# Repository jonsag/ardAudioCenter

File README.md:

# ardAudioCenter

An arduino used as a center for audio control.  
Selects between inputs, sets volume, balance etc.  
Controls an FM radio receiver.  
Has an LCD screen.  

## Note

This is a work in progress, but should now be working.  

## Parts list (incomplete)

1 x Arduino (I use and Arduino Nano, ElectroKit#41015511)  
1 x TEA5767 FM radio module, ElectroKit#41015747  
1 x DFPlayer Mini  
1 x CD4052B multiplexer, ElectroKit#40360102  
2 x MCP41010-E/P digital potentiometer, ElectroKit#40351010  
1 x LCD screen, 2x16, ElectroKit#41001407  
1 x Serial interface for LCD, ElectroKit#41011443  
2 x Rotary encoder, ElectroKit#41015725

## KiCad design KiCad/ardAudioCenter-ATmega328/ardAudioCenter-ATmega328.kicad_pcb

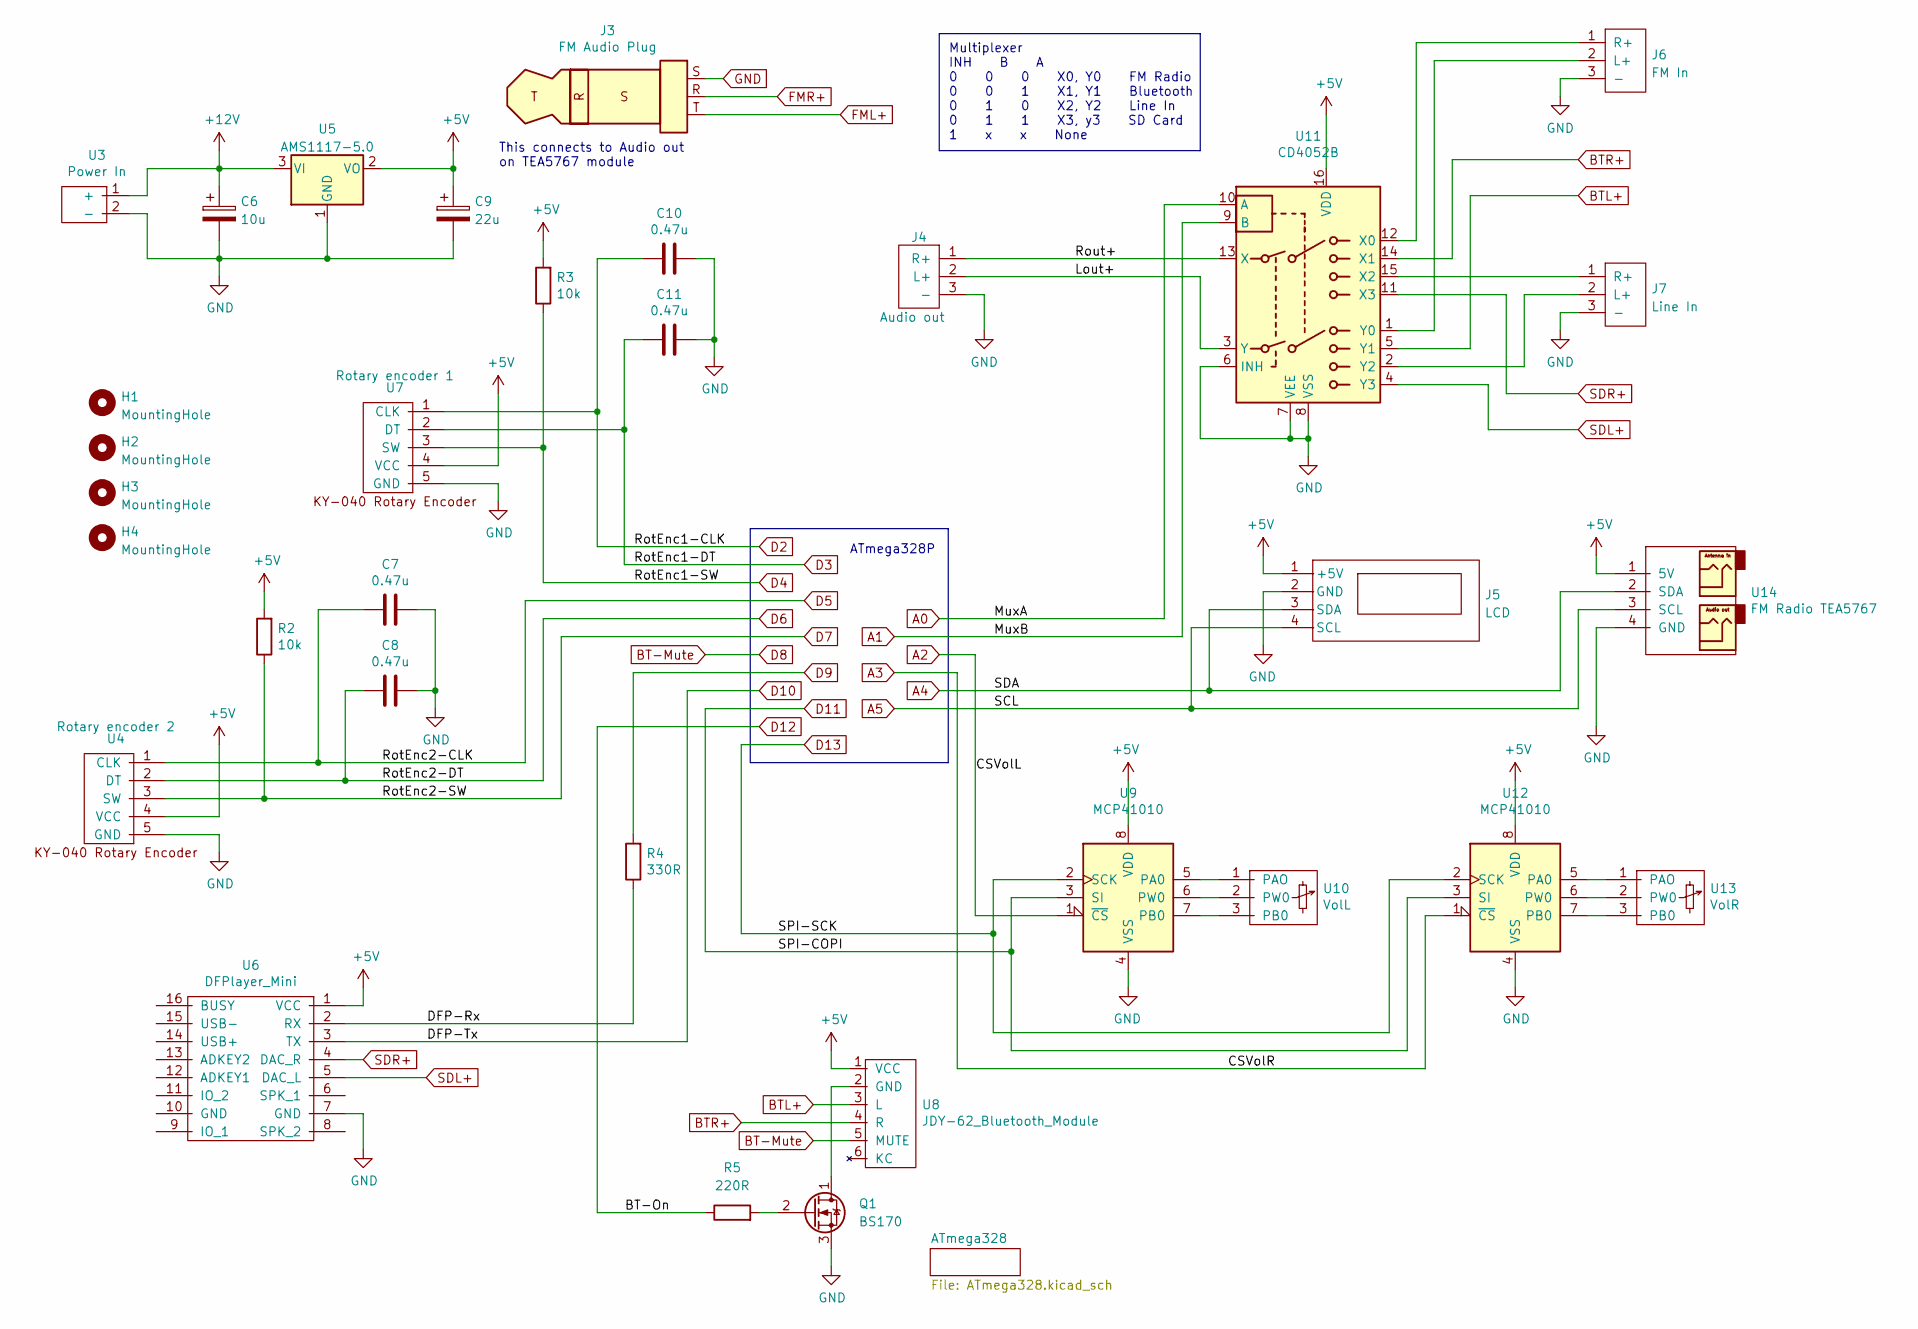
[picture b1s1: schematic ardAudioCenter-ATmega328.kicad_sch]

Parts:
C6: 10u; CP_Radial_D5.0mm_P2.00mm_larger
C7, C8, C10, C11: 0.47u; C_Disc_D7.5mm_W2.5mm_P5.00mm_larger
C9: 22u; CP_Radial_D5.0mm_P2.00mm_larger
H1, H2, H3, H4: MountingHole; MountingHole_3.5mm
J3: FM Audio Plug
J4: Audio out; 3-pin JST Audio
J5: LCD; 4-pin JST LCD
J6: FM In; 3-pin JST Audio
J7: Line In; 3-pin JST Audio
Q1: BS170; TO-92_Inline_Wide_large
R2, R3: 10k; R_Axial_DIN0207_L6.3mm_D2.5mm_P10.16mm_Horizontal_larger_pa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
R4: 330R; R_Axial_DIN0207_L6.3mm_D2.5mm_P10.16mm_Horizontal_larger_pa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
R5: 220R; R_Axial_DIN0207_L6.3mm_D2.5mm_P10.16mm_Horizontal_larger_pa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
U3: Power In; 2-pole_power_in_screw_terminal
U4: Rotary encoder 2; 5-pin JST Rotary Encoder
U5: AMS1117-5.0; SOT-223-3_TabPin2
U6: DFPlayer_Mini; 8-pin JST DFPlayer Mini
U7: Rotary encoder 1; 5-pin JST Rotary Encoder
U8: JDY-62_Bluetooth_Module; 6-pin JST JDY-62 Bluetooth
U9, U12: MCP41010; DIP-8_W7.62mm_Socket_w_dip_packet_LongPads
U10: VolL; 3-pin JST Potentiometer
U11: CD4052B; DIP-16_W7.62mm_LongPads w socket
U13: VolR; 3-pin JST Potentiometer
U14: FM Radio TEA5767; 4-pin JST TEA5767 FM Radio

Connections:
+5V: C9.1, J5.1 (+5V), R2.2, R3.2, U4.4 (VCC), U5.2 (VO), U6.1 (VCC), U7.4 (VCC), U8.1 (VCC), U9.8 (VDD), U11.16 (VDD), U12.8 (VDD), U14.1 (5V); also elsewhere on the board
+12V: C6.1, U3.1 (+), U5.3 (VI)
/DFP-Rx: R4.1, U6.2 (RX)
/Lout+: J4.2 (L+), U11.3 (Y)
/Rout+: J4.1 (R+), U11.13 (X)
A0: U11.10 (A); also elsewhere on the board
A1: U11.9 (B); also elsewhere on the board
A2: U9.1 (~CS); also elsewhere on the board
A3: U12.1 (~CS); also elsewhere on the board
A4: J5.3 (SDA), U14.2 (SDA); also elsewhere on the board
A5: J5.4 (SCL), U14.3 (SCL); also elsewhere on the board
BT-Mute: U8.5 (MUTE); also elsewhere on the board
BTL+: U8.3 (L), U11.5 (Y1)
BTR+: U8.4 (R), U11.14 (X1)
D2: C10.1, U7.1 (CLK); also elsewhere on the board
D3: C11.2, U7.2 (DT); also elsewhere on the board
D4: R3.1, U7.3 (SW); also elsewhere on the board
D5: C7.1, U4.1 (CLK); also elsewhere on the board
D6: C8.2, U4.2 (DT); also elsewhere on the board
D7: R2.1, U4.3 (SW); also elsewhere on the board
D9: R4.2; also elsewhere on the board
D10: U6.3 (TX); also elsewhere on the board
D11: U9.3 (SI), U12.3 (SI); also elsewhere on the board
D12: R5.1; also elsewhere on the board
D13: U9.2 (SCK), U12.2 (SCK); also elsewhere on the board
GND: C6.2, C7.2, C8.1, C9.2, C10.2, C11.1, J4.3 (-), J5.2 (GND), J6.3 (-), J7.3 (-), Q1.3 (S), U3.2 (-), U4.5 (GND), U5.1 (GND), U6.7 (GND), U7.5 (GND), U9.4 (VSS), U11.6 (INH), U11.7 (VEE), U11.8 (VSS), U12.4 (VSS), U14.4 (GND); also elsewhere on the board
unnamed: J6.1 (R+), U11.12 (X0)
unnamed: J6.2 (L+), U11.1 (Y0)
unnamed: J7.1 (R+), U11.15 (X2)
unnamed: J7.2 (L+), U11.2 (Y2)
unnamed: Q1.1 (D), U8.2 (GND)
unnamed: Q1.2 (G), R5.2
unnamed: U9.5 (PA0), U10.1 (PAO)
unnamed: U9.6 (PW0), U10.2 (PW0)
unnamed: U9.7 (PB0), U10.3 (PB0)
unnamed: U12.5 (PA0), U13.1 (PAO)
unnamed: U12.6 (PW0), U13.2 (PW0)
unnamed: U12.7 (PB0), U13.3 (PB0)
SDL+: U6.5 (DAC_L), U11.4 (Y3)
SDR+: U6.4 (DAC_R), U11.11 (X3)

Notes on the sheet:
This connects to Audio out on TEA5767 module
ATmega328P
Multiplexer INH B A 0 0 0 X0, Y0 FM Radio 0 0 1 X1, Y1 Bluetooth 0 1 0 X2, Y2 Line In 0 1 1 X3, y3 SD Card 1 x x None

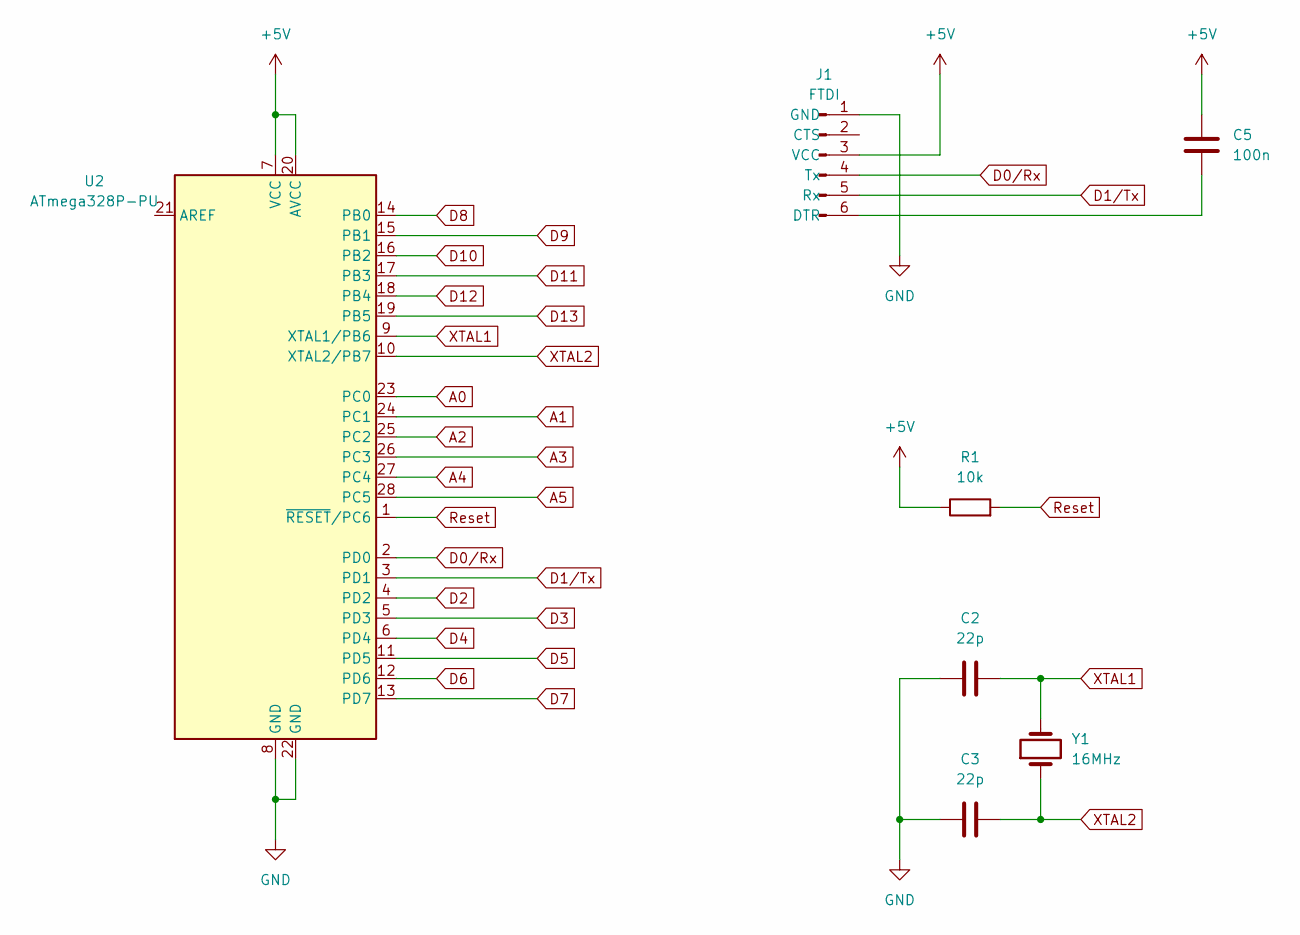
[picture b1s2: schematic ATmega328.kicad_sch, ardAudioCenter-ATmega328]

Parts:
C2, C3: 22p; C_Disc_D3.0mm_W1.6mm_P2.50mm_larg
C5: 100n; C_Disc_D3.0mm_W1.6mm_P2.50mm_larg
J1: FTDI; 6-pin FTDI Programmer PinSocket large
R1: 10k; R_Axial_DIN0207_L6.3mm_D2.5mm_P10.16mm_Horizontal_larger_pa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
U2: ATmega328P-PU; DIP-28_W7.62mm_LongPads w socket
Y1: 16MHz; Crystal_HC49-4H_Vertical_large

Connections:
+5V: C5.2, J1.3 (VCC), R1.1, U2.7 (VCC), U2.20 (AVCC); also elsewhere on the board
A0: U2.23 (PC0); also elsewhere on the board
A1: U2.24 (PC1); also elsewhere on the board
A2: U2.25 (PC2); also elsewhere on the board
A3: U2.26 (PC3); also elsewhere on the board
A4: U2.27 (PC4); also elsewhere on the board
A5: U2.28 (PC5); also elsewhere on the board
BT-Mute: U2.14 (PB0); also elsewhere on the board
D0/Rx: J1.4 (Tx), U2.2 (PD0)
D1/Tx: J1.5 (Rx), U2.3 (PD1)
D2: U2.4 (PD2); also elsewhere on the board
D3: U2.5 (PD3); also elsewhere on the board
D4: U2.6 (PD4); also elsewhere on the board
D5: U2.11 (PD5); also elsewhere on the board
D6: U2.12 (PD6); also elsewhere on the board
D7: U2.13 (PD7); also elsewhere on the board
D9: U2.15 (PB1); also elsewhere on the board
D10: U2.16 (PB2); also elsewhere on the board
D11: U2.17 (PB3); also elsewhere on the board
D12: U2.18 (PB4); also elsewhere on the board
D13: U2.19 (PB5); also elsewhere on the board
GND: C2.1, C3.1, J1.1 (GND), U2.8 (GND), U2.22 (GND); also elsewhere on the board
unnamed: C5.1, J1.6 (DTR)
Reset: R1.2, U2.1 (~RESET/PC6)
XTAL1: C2.2, U2.9 (XTAL1/PB6), Y1.2
XTAL2: C3.2, U2.10 (XTAL2/PB7), Y1.1

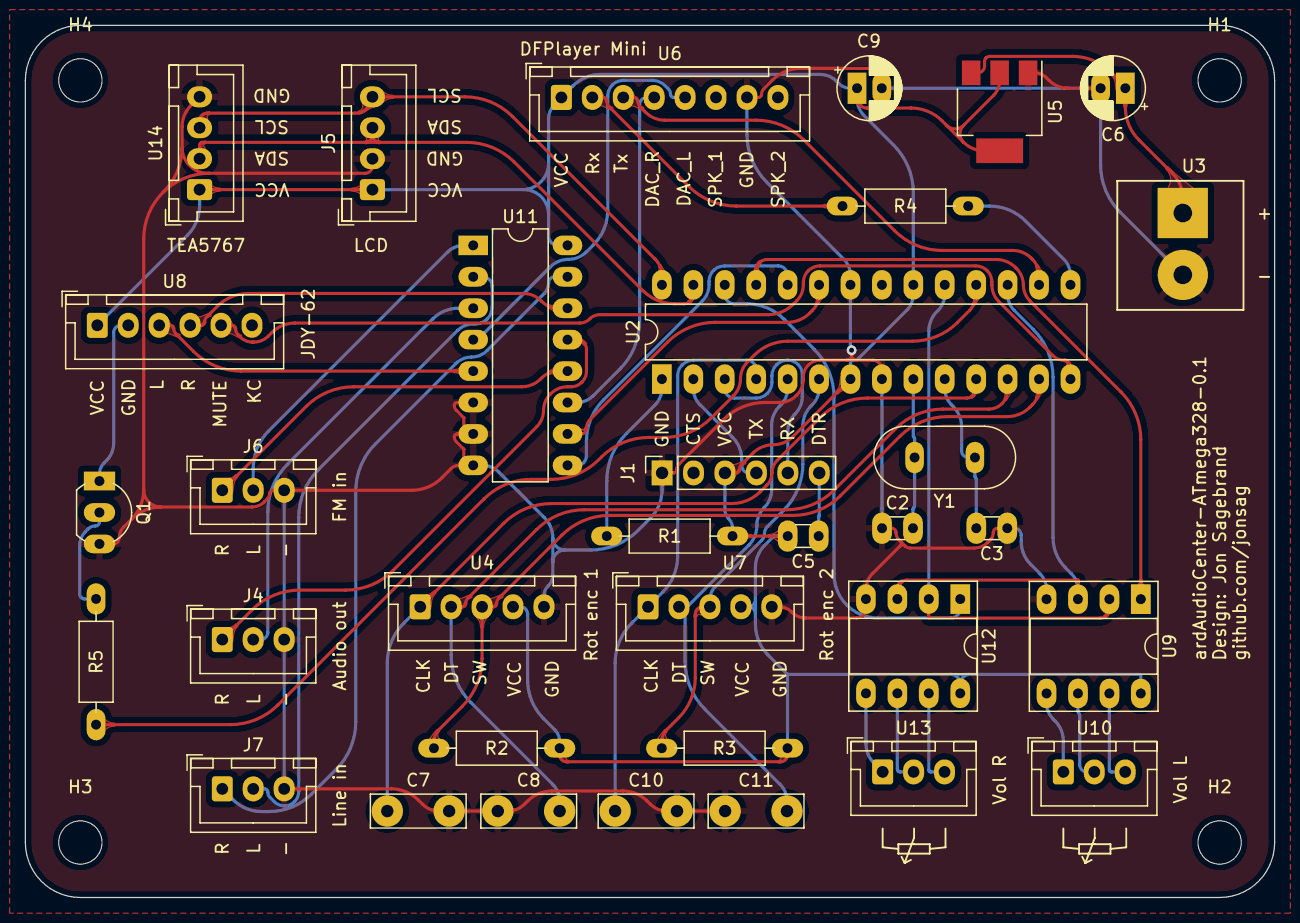
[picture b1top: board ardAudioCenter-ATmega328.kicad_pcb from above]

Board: 2 copper layers, 101.0 x 70.5 mm, 38 parts (0 on the bottom side), 46 nets.

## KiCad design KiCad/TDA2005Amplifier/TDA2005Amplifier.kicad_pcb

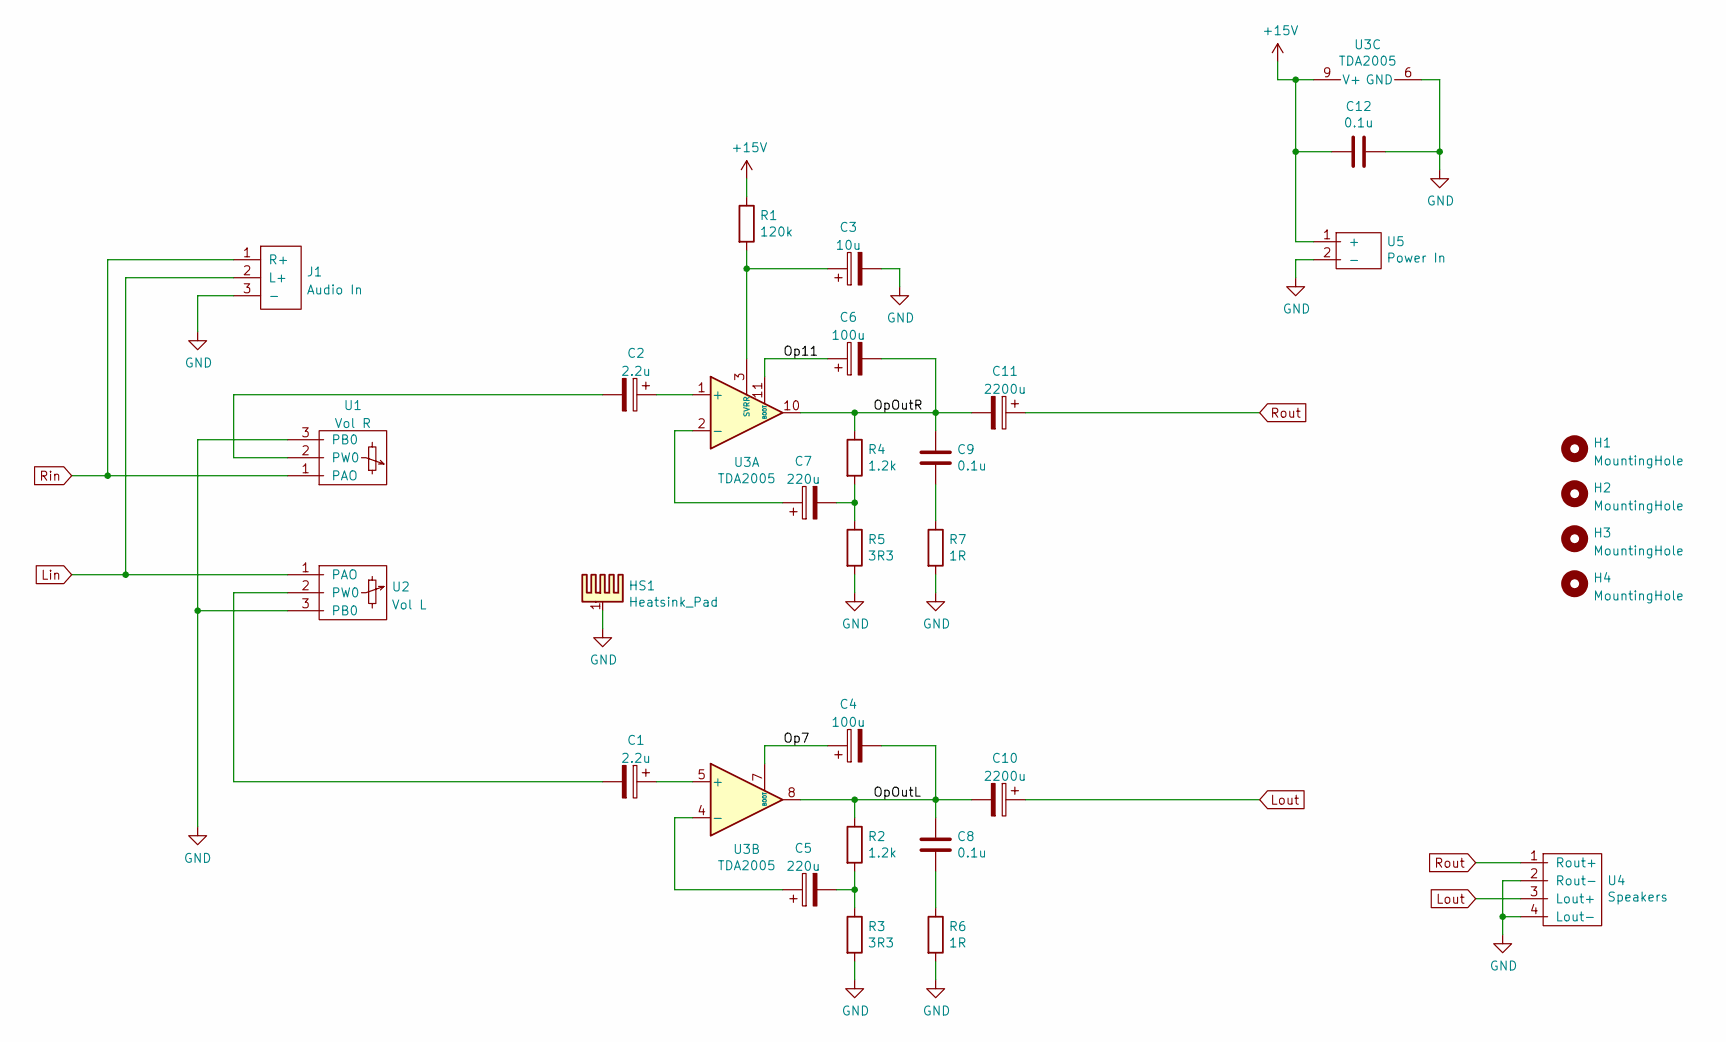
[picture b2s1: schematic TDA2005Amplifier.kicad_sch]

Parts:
C1, C2: 2.2u; CP_Radial_D5.0mm_P2.00mm_larger
C3: 10u; CP_Radial_D5.0mm_P2.00mm_larger
C4, C6: 100u; CP_Radial_D5.0mm_P2.50mm_larger_pads
C5, C7: 220u; CP_Radial_D8.0mm_P3.50mm_large
C8, C9, C12: 0.1u; C_Disc_D7.5mm_W2.5mm_P5.00mm_larger
C10, C11: 2200u; CP_Radial_D13.0mm_P5.00mm_larger
H1, H2, H3, H4: MountingHole; MountingHole_3.2mm_M3
HS1: Heatsink_Pad; EK-41002859
J1: Audio In; 3-pin JST Audio
R1: 120k; R_Axial_DIN0414_L11.9mm_D4.5mm_P15.24mm_Horizontal_larger
R2, R4: 1.2k; R_Axial_DIN0414_L11.9mm_D4.5mm_P15.24mm_Horizontal_larger
R3, R5: 3R3; R_Axial_DIN0414_L11.9mm_D4.5mm_P15.24mm_Horizontal_larger
R6, R7: 1R; R_Axial_DIN0414_L11.9mm_D4.5mm_P15.24mm_Horizontal_larger
U1: Vol R; 3-pin JST Potentiometer
U2: Vol L; 3-pin JST Potentiometer
U3: TDA2005; TO-220-11_P3.4x5.08mm_StaggerOdd_Lead4.85mm_Vertical_large
U4: Speakers; 4-pole_screw_terminal_RL_output
U5: Power In; 2-pole_power_in_screw_terminal

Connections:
+15V: C12.2, R1.1, U3.9 (V+), U5.1 (+)
/Op7: C4.1, U3.7 (BOOT)
/Op11: C6.1, U3.11 (BOOT)
/OpOutL: C4.2, C8.1, C10.2, R2.1, U3.8
/OpOutR: C6.2, C9.1, C11.2, R4.1, U3.10
GND: C3.2, C12.1, HS1.1, J1.3 (-), R3.2, R5.2, R6.2, R7.2, U1.3 (PB0), U2.3 (PB0), U3.6 (GND), U4.2 (Rout-), U4.4 (Lout-), U5.2 (-)
Lin: J1.2 (L+), U2.1 (PAO)
Lout: C10.1, U4.3 (Lout+)
unnamed: C1.1, U3.5 (+)
unnamed: C1.2, U2.2 (PW0)
unnamed: C2.1, U3.1 (+)
unnamed: C2.2, U1.2 (PW0)
unnamed: C3.1, R1.2, U3.3 (SVRR)
unnamed: C5.1, U3.4 (-)
unnamed: C5.2, R2.2, R3.1
unnamed: C7.1, U3.2 (-)
unnamed: C7.2, R4.2, R5.1
unnamed: C8.2, R6.1
unnamed: C9.2, R7.1
Rin: J1.1 (R+), U1.1 (PAO)
Rout: C11.1, U4.1 (Rout+)

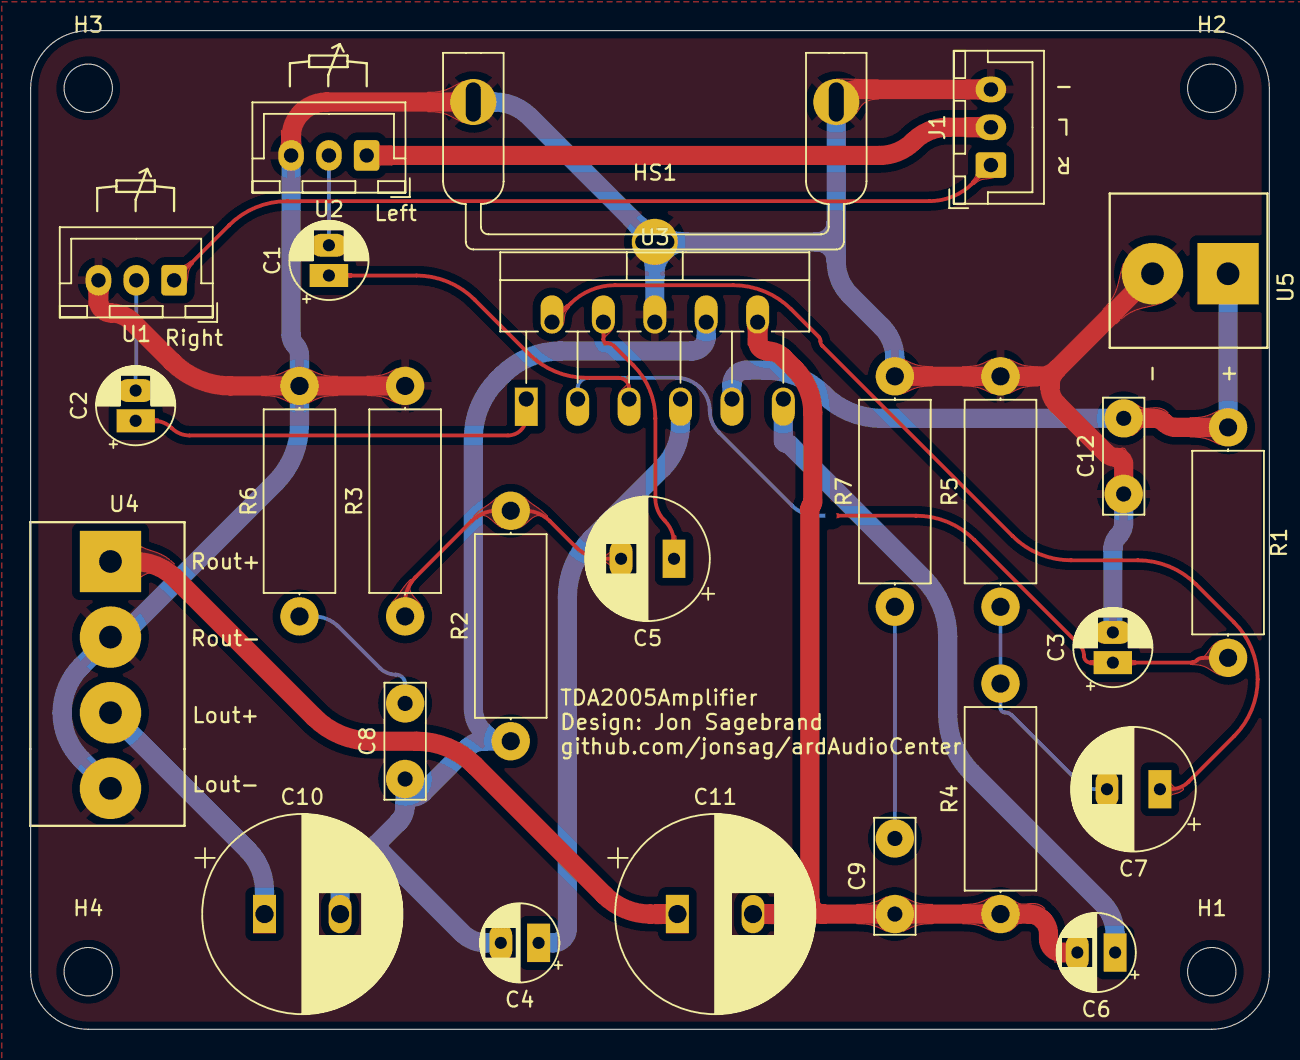
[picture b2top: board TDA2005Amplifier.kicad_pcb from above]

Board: 2 copper layers, 81.9 x 66.0 mm, 30 parts (0 on the bottom side), 21 nets.

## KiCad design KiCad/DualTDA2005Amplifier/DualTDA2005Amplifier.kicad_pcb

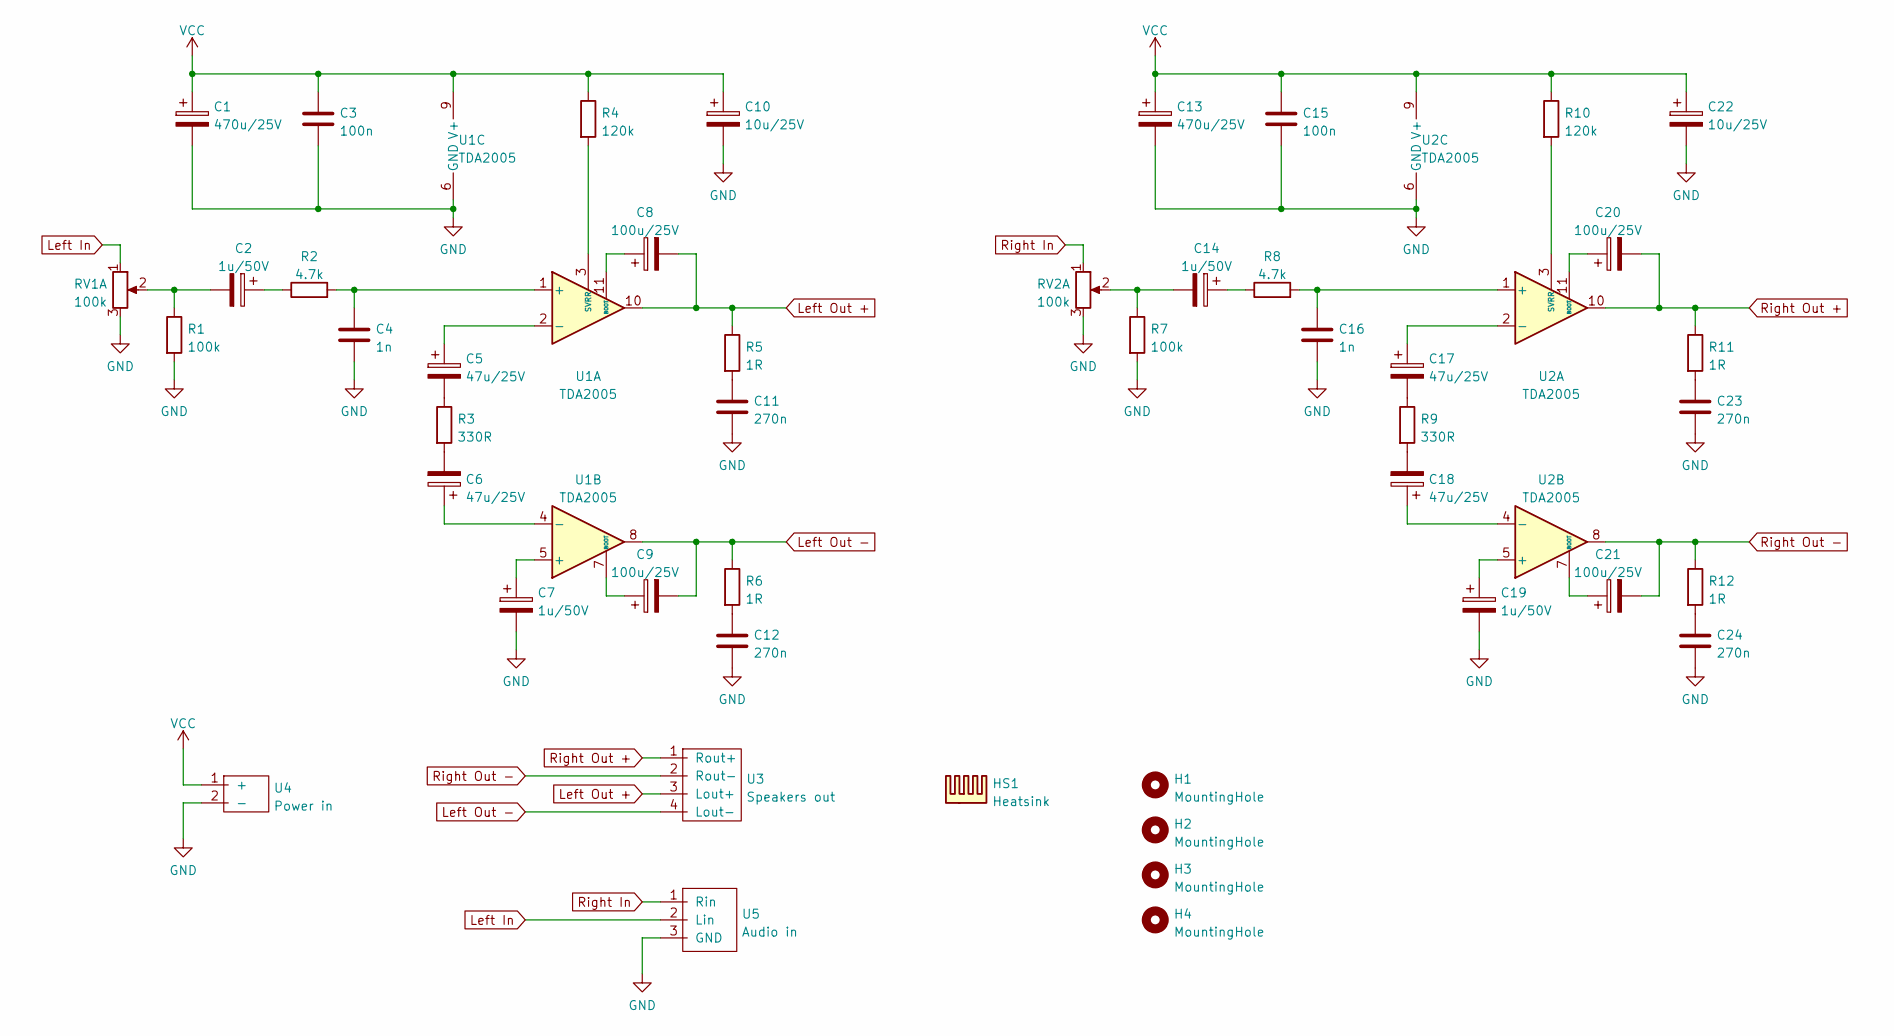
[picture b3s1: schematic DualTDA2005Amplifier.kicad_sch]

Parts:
C1, C13: 470u/25V; CP_Radial_D10.0mm_P5.00mm_larger
C2, C7, C14, C19: 1u/50V; CP_Radial_D5.0mm_P2.00mm_larger
C3, C15: 100n; C_Rect_L7.2mm_W2.5mm_P5.00mm_FKS2_FKP2_MKS2_MKP2 large
C4, C16: 1n; C_Rect_L7.2mm_W2.5mm_P5.00mm_FKS2_FKP2_MKS2_MKP2 large
C5, C6, C17, C18: 47u/25V; CP_Radial_D5.0mm_P2.00mm_larger
C8, C9, C20, C21: 100u/25V; CP_Radial_D6.3mm_P2.50mm_large
C10, C22: 10u/25V; CP_Radial_D5.0mm_P2.00mm_larger
C11, C12, C23, C24: 270n; C_Rect_L7.2mm_W3.5mm_P5.00mm_FKS2_FKP2_MKS2_MKP2 large
H1, H2, H3, H4: MountingHole; MountingHole_3.2mm_M3
HS1: Heatsink; Heatsink SK81 100x37.5x15
R1, R7: 100k; R_Axial_DIN0207_L6.3mm_D2.5mm_P10.16mm_Horizontal_larger_pa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
R2, R8: 4.7k; R_Axial_DIN0207_L6.3mm_D2.5mm_P10.16mm_Horizontal_larger_pa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
R3, R9: 330R; R_Axial_DIN0207_L6.3mm_D2.5mm_P10.16mm_Horizontal_larger_pa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
R4, R10: 120k; R_Axial_DIN0207_L6.3mm_D2.5mm_P10.16mm_Horizontal_larger_pa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
R5, R6, R11, R12: 1R; R_Axial_DIN0207_L6.3mm_D2.5mm_P10.16mm_Horizontal_larger_pa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
RV1, RV2: 100k; 3-pin JST Potentiometer
U1, U2: TDA2005; TO-220-11_P3.4x5.08mm_StaggerOdd_Lead4.85mm_Vertical_large
U3: Speakers out; 4-pole_screw_terminal_RL_output
U4: Power in; 2-pole_power_in_screw_terminal
U5: Audio in; 3-pin JST Audio

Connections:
GND: C1.2, C3.2, C4.2, C7.2, C10.2, C11.2, C12.2, C13.2, C15.2, C16.2, C19.2, C22.2, C23.2, C24.2, R1.2, R7.2, RV1.3, RV2.3, U1.6 (GND), U2.6 (GND), U4.2 (-), U5.3 (GND)
Left In: RV1.1, U5.2 (Lin)
Left Out +: C8.2, R5.1, U1.10, U3.3 (Lout+)
Left Out -: C9.2, R6.1, U1.8, U3.4 (Lout-)
unnamed: C2.1, R2.1
unnamed: C2.2, R1.1, RV1.2
unnamed: C4.1, R2.2, U1.1 (+)
unnamed: C5.1, U1.2 (-)
unnamed: C5.2, R3.1
unnamed: C6.1, U1.4 (-)
unnamed: C6.2, R3.2
unnamed: C7.1, U1.5 (+)
unnamed: C8.1, U1.11 (BOOT)
unnamed: C9.1, U1.7 (BOOT)
unnamed: C11.1, R5.2
unnamed: C12.1, R6.2
unnamed: C14.1, R8.1
unnamed: C14.2, R7.1, RV2.2
unnamed: C16.1, R8.2, U2.1 (+)
unnamed: C17.1, U2.2 (-)
unnamed: C17.2, R9.1
unnamed: C18.1, U2.4 (-)
unnamed: C18.2, R9.2
unnamed: C19.1, U2.5 (+)
unnamed: C20.1, U2.11 (BOOT)
unnamed: C21.1, U2.7 (BOOT)
unnamed: C23.1, R11.2
unnamed: C24.1, R12.2
unnamed: R4.2, U1.3 (SVRR)
unnamed: R10.2, U2.3 (SVRR)
Right In: RV2.1, U5.1 (Rin)
Right Out +: C20.2, R11.1, U2.10, U3.1 (Rout+)
Right Out -: C21.2, R12.1, U2.8, U3.2 (Rout-)
VCC: C1.1, C3.1, C10.1, C13.1, C15.1, C22.1, R4.1, R10.1, U1.9 (V+), U2.9 (V+), U4.1 (+)

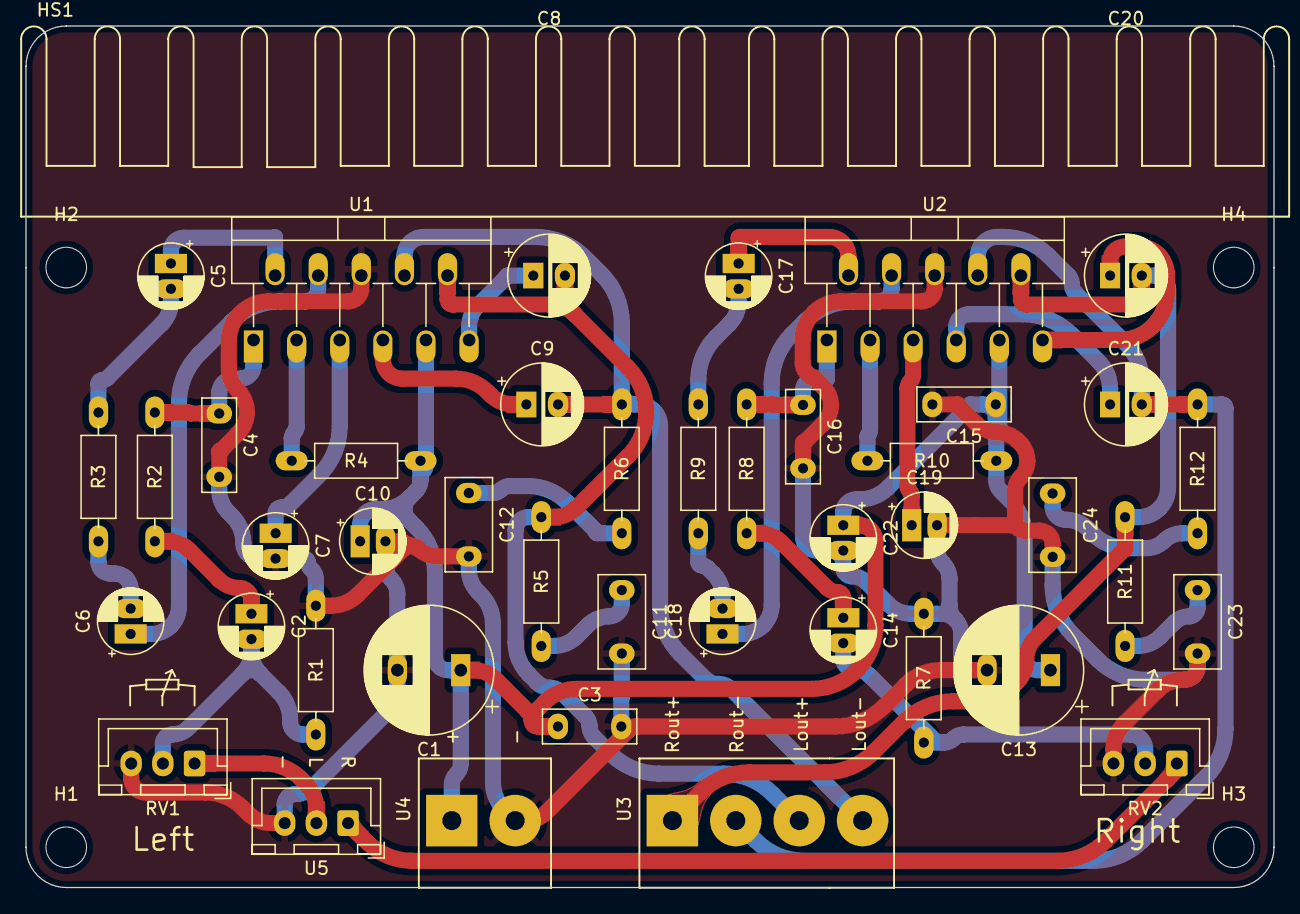
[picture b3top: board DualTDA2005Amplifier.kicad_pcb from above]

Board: 2 copper layers, 98.4 x 67.9 mm, 48 parts (0 on the bottom side), 34 nets.

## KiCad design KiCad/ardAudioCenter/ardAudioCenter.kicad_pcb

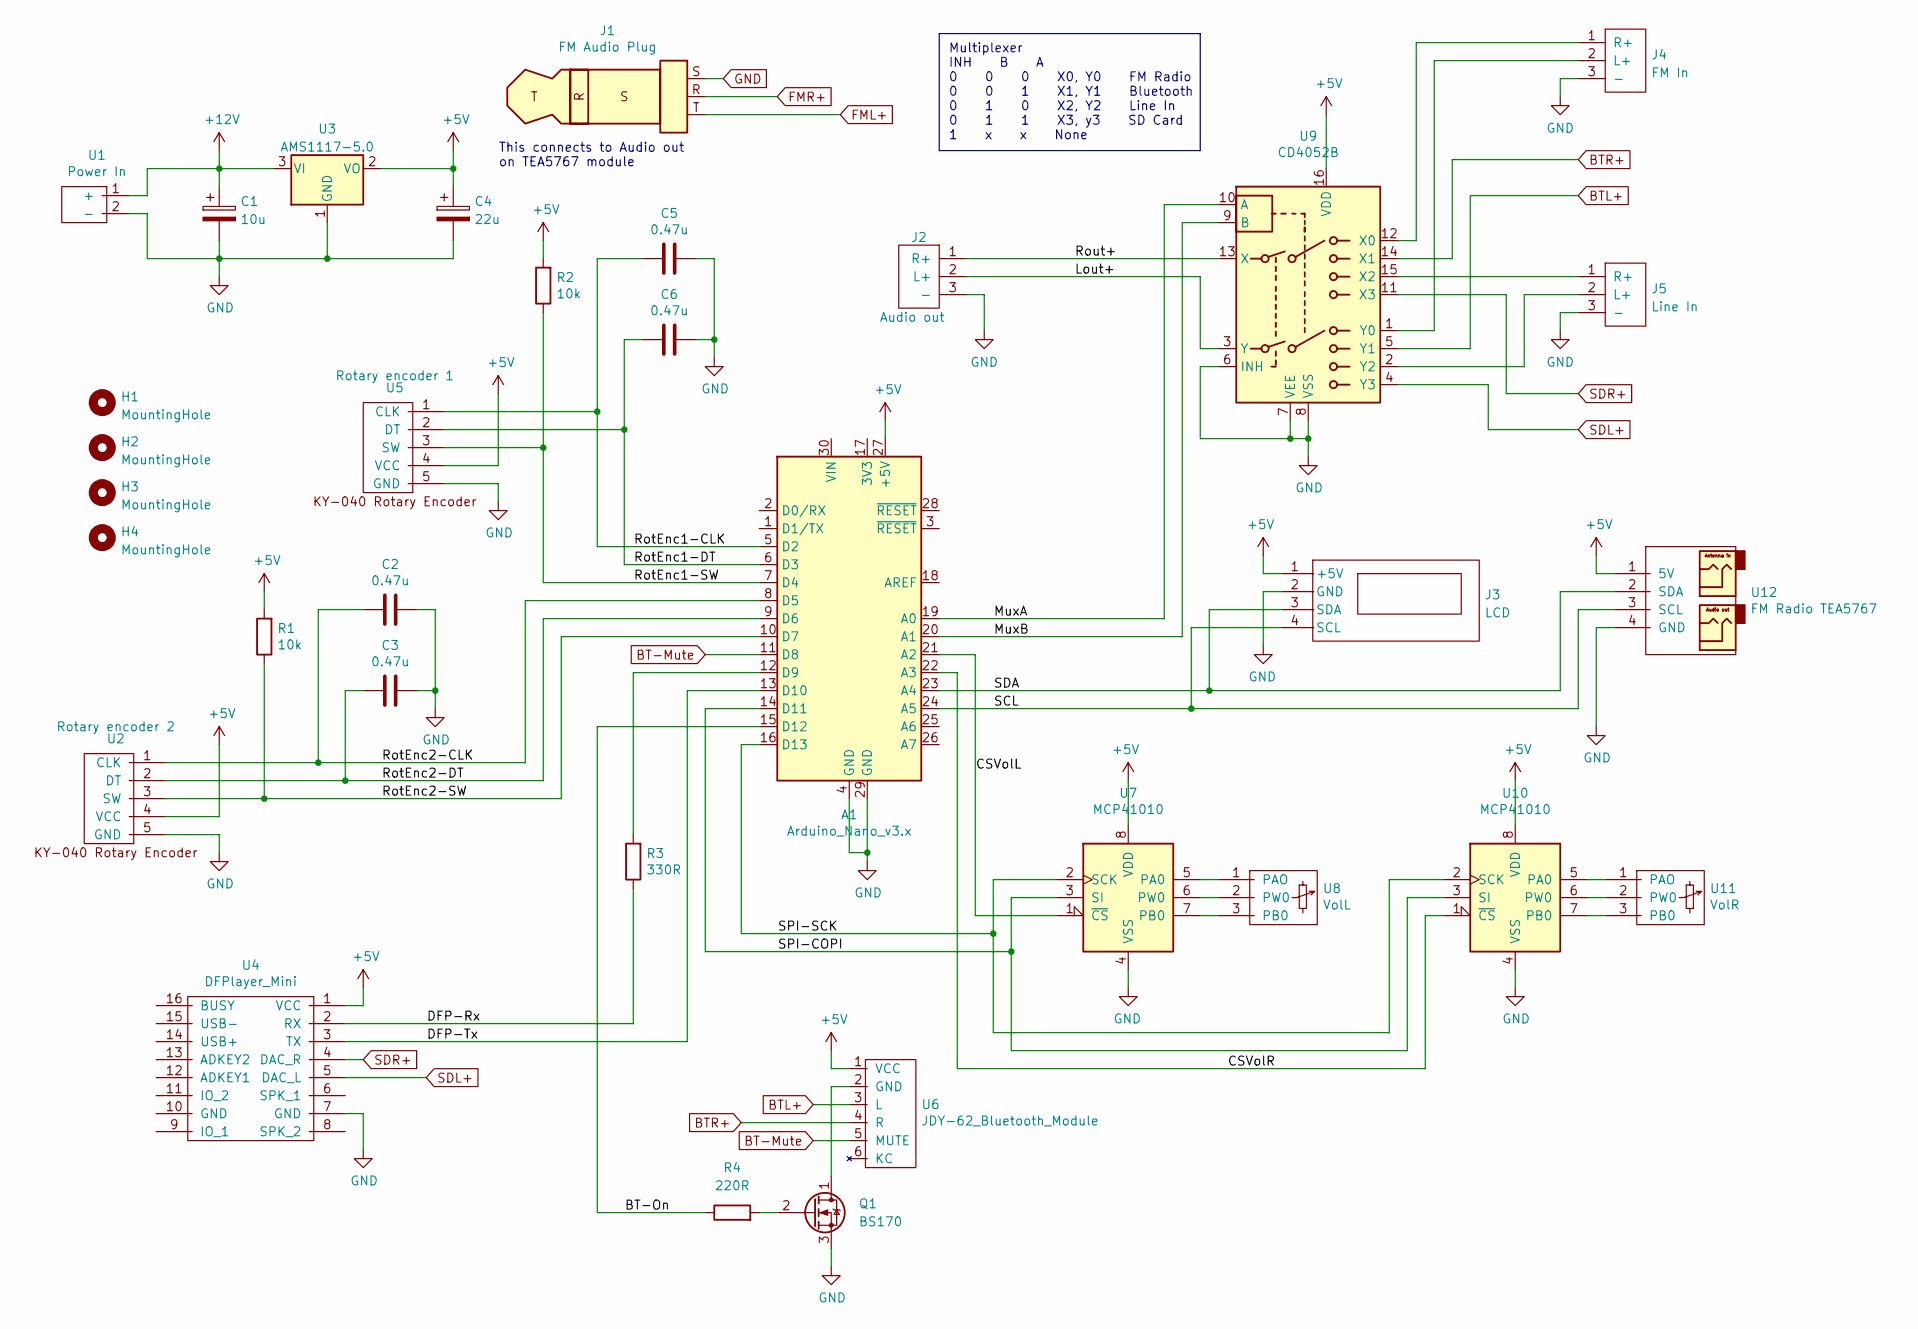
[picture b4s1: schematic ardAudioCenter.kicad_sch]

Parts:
A1: Arduino_Nano_v3.x; Arduino_Nano_WithMountingHoles_larger
C1: 10u; CP_Radial_D5.0mm_P2.00mm_larger
C2, C3, C5, C6: 0.47u; C_Disc_D7.5mm_W2.5mm_P5.00mm_larger
C4: 22u; CP_Radial_D5.0mm_P2.00mm_larger
H1, H2, H3, H4: MountingHole; MountingHole_3.5mm
J1: FM Audio Plug
J2: Audio out; 3-pin JST Audio
J3: LCD; 4-pin JST LCD
J4: FM In; 3-pin JST Audio
J5: Line In; 3-pin JST Audio
Q1: BS170; TO-92_Inline_Wide_large
R1, R2: 10k; R_Axial_DIN0207_L6.3mm_D2.5mm_P10.16mm_Horizontal_larger_pa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
R3: 330R; R_Axial_DIN0207_L6.3mm_D2.5mm_P10.16mm_Horizontal_larger_pa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
R4: 220R; R_Axial_DIN0207_L6.3mm_D2.5mm_P10.16mm_Horizontal_larger_pa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
U1: Power In; 2-pole_power_in_screw_terminal
U2: Rotary encoder 2; 5-pin JST Rotary Encoder
U3: AMS1117-5.0; SOT-223-3_TabPin2
U4: DFPlayer_Mini; 8-pin JST DFPlayer Mini
U5: Rotary encoder 1; 5-pin JST Rotary Encoder
U6: JDY-62_Bluetooth_Module; 6-pin JST JDY-62 Bluetooth
U7, U10: MCP41010; DIP-8_W7.62mm_Socket_w_dip_packet_LongPads
U8: VolL; 3-pin JST Potentiometer
U9: CD4052B; DIP-16_W7.62mm_LongPads w socket
U11: VolR; 3-pin JST Potentiometer
U12: FM Radio TEA5767; 4-pin JST TEA5767 FM Radio

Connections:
+5V: A1.27 (+5V), C4.1, J3.1 (+5V), R1.2, R2.2, U2.4 (VCC), U3.2 (VO), U4.1 (VCC), U5.4 (VCC), U6.1 (VCC), U7.8 (VDD), U9.16 (VDD), U10.8 (VDD), U12.1 (5V)
+12V: C1.1, U1.1 (+), U3.3 (VI)
/BT-On: A1.15 (D12), R4.1
/CSVolL: A1.21 (A2), U7.1 (~CS)
/CSVolR: A1.22 (A3), U10.1 (~CS)
/DFP-Rx: R3.1, U4.2 (RX)
/DFP-Tx: A1.13 (D10), U4.3 (TX)
/Lout+: J2.2 (L+), U9.3 (Y)
/MuxA: A1.19 (A0), U9.10 (A)
/MuxB: A1.20 (A1), U9.9 (B)
/RotEnc1-CLK: A1.5 (D2), C5.1, U5.1 (CLK)
/RotEnc1-DT: A1.6 (D3), C6.2, U5.2 (DT)
/RotEnc1-SW: A1.7 (D4), R2.1, U5.3 (SW)
/RotEnc2-CLK: A1.8 (D5), C2.1, U2.1 (CLK)
/RotEnc2-DT: A1.9 (D6), C3.2, U2.2 (DT)
/RotEnc2-SW: A1.10 (D7), R1.1, U2.3 (SW)
/Rout+: J2.1 (R+), U9.13 (X)
/SCL: A1.24 (A5), J3.4 (SCL), U12.3 (SCL)
/SDA: A1.23 (A4), J3.3 (SDA), U12.2 (SDA)
/SPI-COPI: A1.14 (D11), U7.3 (SI), U10.3 (SI)
/SPI-SCK: A1.16 (D13), U7.2 (SCK), U10.2 (SCK)
BT-Mute: A1.11 (D8), U6.5 (MUTE)
BTL+: U6.3 (L), U9.5 (Y1)
BTR+: U6.4 (R), U9.14 (X1)
GND: A1.4 (GND), A1.29 (GND), C1.2, C2.2, C3.1, C4.2, C5.2, C6.1, J2.3 (-), J3.2 (GND), J4.3 (-), J5.3 (-), Q1.3 (S), U1.2 (-), U2.5 (GND), U3.1 (GND), U4.7 (GND), U5.5 (GND), U7.4 (VSS), U9.6 (INH), U9.7 (VEE), U9.8 (VSS), U10.4 (VSS), U12.4 (GND)
unnamed: A1.12 (D9), R3.2
unnamed: J4.1 (R+), U9.12 (X0)
unnamed: J4.2 (L+), U9.1 (Y0)
unnamed: J5.1 (R+), U9.15 (X2)
unnamed: J5.2 (L+), U9.2 (Y2)
unnamed: Q1.2 (G), R4.2
unnamed: Q1.1 (D), U6.2 (GND)
unnamed: U7.5 (PA0), U8.1 (PAO)
unnamed: U7.6 (PW0), U8.2 (PW0)
unnamed: U7.7 (PB0), U8.3 (PB0)
unnamed: U10.5 (PA0), U11.1 (PAO)
unnamed: U10.6 (PW0), U11.2 (PW0)
unnamed: U10.7 (PB0), U11.3 (PB0)
SDL+: U4.5 (DAC_L), U9.4 (Y3)
SDR+: U4.4 (DAC_R), U9.11 (X3)

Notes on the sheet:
This connects to Audio out on TEA5767 module
Multiplexer INH B A 0 0 0 X0, Y0 FM Radio 0 0 1 X1, Y1 Bluetooth 0 1 0 X2, Y2 Line In 0 1 1 X3, y3 SD Card 1 x x None

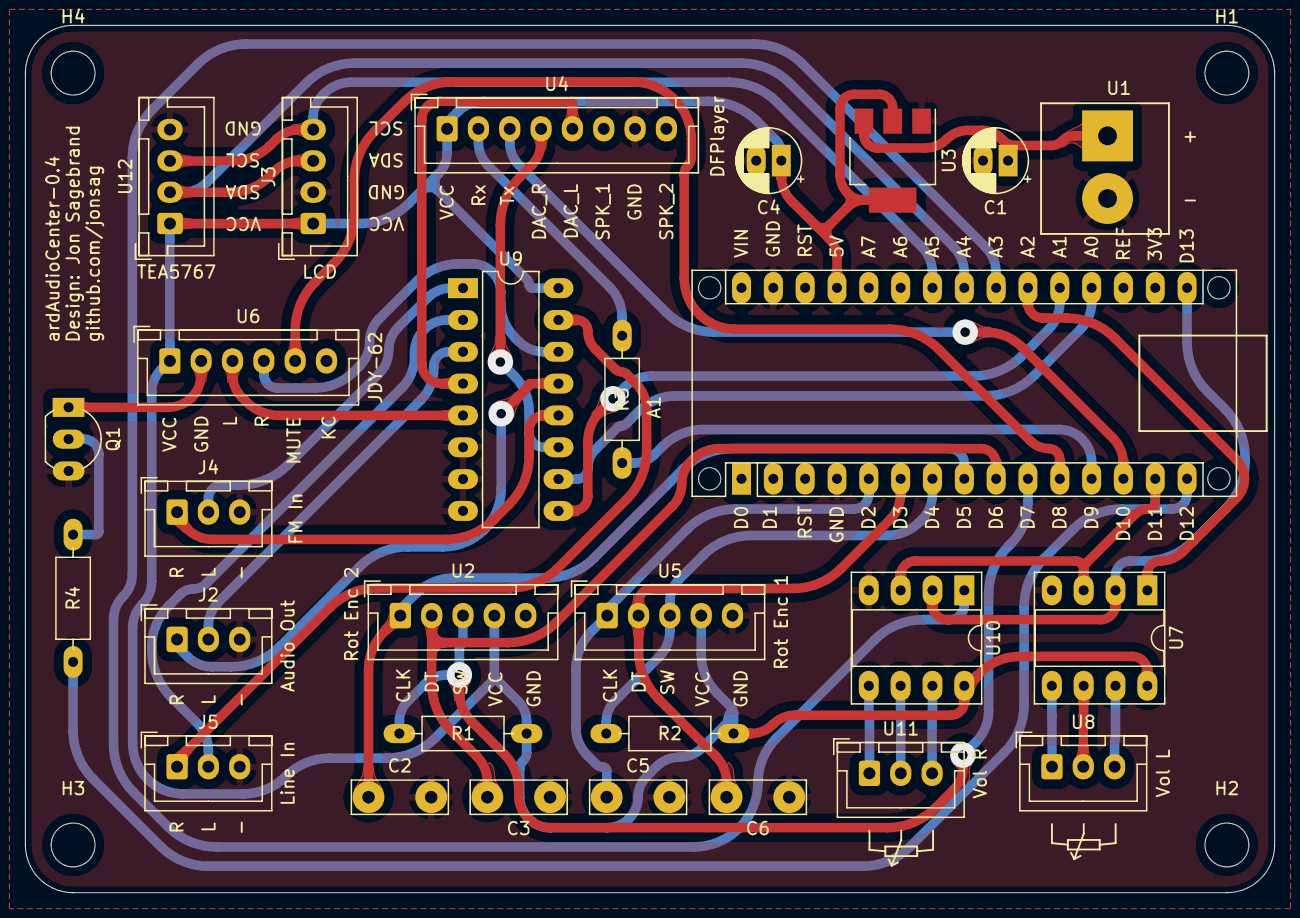
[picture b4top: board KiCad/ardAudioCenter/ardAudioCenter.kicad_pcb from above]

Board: 2 copper layers, 99.7 x 69.2 mm, 32 parts (0 on the bottom side), 40 nets.
